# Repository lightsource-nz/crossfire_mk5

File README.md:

# crossfire

USB-MIDI forwarding between every instrument on the host port, with a small OLED status display.
Two tangible boards run it: a Pico 2 wearing the Pico-OLED-1.3, and the stock RP2040 Pico.

## Building

This project is built against the **light framework** checkout beside it (`../light_mk5`); set
`LIGHT_PATH` for another layout. The framework supplies the C shell, the portable crates, the
ports, the asset compilers and the shared script layer. Everything that is crossfire's own --
the application, the board modules, the version, the signing key, the flash map -- is here.

```
scripts/build.ps1 [-Target crossfire_pico2|crossfire_pico]
scripts/flash.ps1 -Target crossfire_pico2     # over SWD, through a debug probe
scripts/debug.ps1 -Target crossfire_pico2
scripts/console.ps1 -Port <COM>               # the console rides the probe's UART
scripts/test.ps1                              # the application's host tests
```

CI (`.github/workflows/ci.yml`) runs the same scripts through the framework's reusable workflows:
the host tests, and a firmware build of each board -- the Pico 2 leg with its bootloader -- whose
images are kept as artifacts.

## Images are signed

Every build signs its image and the device's flash map with `keys/dev.pem`, which is public and
protects nothing (see `keys/README.md`); a release is signed with a key that never appears here.
The flash map gives the application an A/B pair, so an update is written to the slot that is not
running and chosen on the next boot, and a data partition for the assets. What the hardware
verifies, and when, is specified in the framework's `documents/11-secure-boot-and-update.md`.

## A new image keeps itself only if it works

An update is started on probation: the Pico 2's boot ROM runs it once, and unless it commits itself
the previous image boots again -- at the next reset, or when the ROM's probation watchdog runs out
some seventeen seconds after the boot. crossfire makes that decision on its own
(`crates/light_app_crossfire/src/probation.rs`). At boot the board asks the ROM whether the running
image is a candidate; if so, the application watches itself for three seconds after every module has
loaded and commits once the main loop is turning over, the console core is alive, and the display
has taken a whole frame with no bus timeout. A panic, a stopped loop or a failed check means no
commit, and so the old firmware comes back; a candidate that has not passed by ten seconds of uptime
is given up on well inside the ROM's window. The console reports every step as `probation: ...`.
The RP2040 has no second slot and puts nothing on probation, so there every image is already kept.

## The production board

`pcb/` holds the hardware for the board this firmware is heading for -- an RP2350 hosting four
instruments through a hub, powered over USB-C, optionally with a radio and a battery. It is a KiCad
project with the blocks and their interfaces settled and no components placed yet, alongside the
power budget, the part selection and the two decisions the rest of the design hangs off. See
`pcb/README.md`. Nothing has been built or measured.

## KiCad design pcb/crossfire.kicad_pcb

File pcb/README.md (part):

# crossfire hardware

The production board: an RP2350 hosting four USB instruments through a hub, with one USB-C
connector that carries both its power and its link to a computer.

**Status: prototype, nothing built.** Every number below is a budget or a datasheet figure, not a
measurement. A predecessor design exists elsewhere as a sketch of an earlier vision; it was never
manufactured or validated, so nothing here is inherited from it — individual parts are reused only
where they stand up on their own.

**This is the reduced first design.** An earlier revision of this board carried a Power Delivery
sink on a second connector, a charger and a cell, and a radio. Those are deferred, not rejected: they
made a first board that was hard to lay out and harder to bring up, and none of them is needed to
prove the thing the product is for. That revision is kept whole in the history at commit `bb66643`.

## What the board has to do

- Host four USB-MIDI instruments at once, on four type-A receptacles, each supplied from the
  board's 5 V input.
- Keep the firmware that already exists: the USB device role and its console, and the signed A/B
  image pair with probation.
- Present itself to a computer on the upstream connector *while* hosting the instruments, so the two
  roles live on separate interfaces.
- Take all of its power from that same upstream USB-C connector, and share out whatever the source
  there offers between the four ports and its own electronics.

## Three decisions shape everything else

### 1. Two USB roles on two interfaces

The RP2350 has **one** USB controller, and the board needs two roles at once: host for the four
instruments, device for the computer on the upstream connector. The roles are kept apart on separate
interfaces — the hardware controller takes one, and a full-speed port built in PIO takes the other.
Nothing is multiplexed and nothing switches role, so a computer and the instruments are live at the
same time.

**The hardware controller faces outward as the device, and PIO hosts the hub.** The deciding
argument is recovery, and it beats the alternative on its own terms:

- **The boot ROM drives the hardware controller.** Putting that pair on the upstream connector means
  BOOTSEL and USB DFU work on the connector the product actually has. Recovery needs no debug probe,
  no case opened, nobody on the bench.
- **It makes the risky new thing the recoverable one.** The host side is what has to be rebuilt, and
  if that goes wrong the board can still be reflashed over its own port. The other way round, a rough
  device port takes the console and DFU with it and leaves only SWD.
- **Bring-up starts working rather than blocked.** The board is programmable and has a console over
  its own connector before any of the new firmware exists, so the host side can be brought up
  incrementally against a board that already talks.

What it costs, plainly: **the host role moves onto a new transport.** The existing host stack sits
behind a host-controller seam, so the stack, the hub handling and the MIDI layer above it are kept —
but the packet-level transport underneath becomes a full-speed USB host built in PIO, which does not
exist in this tree. That is the single largest piece of new firmware this board asks for, and it is
the harder of the two roles to build: it has to generate frames, schedule transactions across four
devices and a hub, and handle retries.

The device side, by contrast, is already proven on hardware — the console rides it today. The one
addition there is the computer-facing MIDI interface, which is a device class on a working stack.

**The upstream connector is unambiguous.** It sinks power and acts as a device, both, always — so
the CC lines mean one thing, there is no role to choose, and the charger-versus-computer guess that a
multiplexed design would have needed is gone. Electrically it is also the simpler end: the hardware
controller's pins carry their own impedance matching and pull-ups, so the pair needs only an ESD
array and the receptacle's two data pairs tied together, so a cable can go in either way up.

**The PIO port sets the system clock, and it sets it upward: 240 MHz.** Full-speed bit timing off PIO
wants a system clock that is an integer multiple of 12 MHz, so the state-machine divider is exact and
the bit period carries no fractional jitter. The stock 150 MHz is not such a multiple. Going *down* to
120 MHz would satisfy it at the cost of a fifth of the loop; going up to 240 MHz satisfies it and buys
the loop instead, and four things line up on that number:

- **12 MHz × 20.** Twenty system cycles per bit, and an exact divide by two if the state machine wants
  to run at 120 MHz. Either way the divider is an integer.
- **Twenty cycles a bit is a generous instruction budget** for the hardest software on the board. Ten
  would have been tight. The clock that makes the timing legal also makes the program easier to write.
- **It is already proven on this silicon.** A board in this codebase runs RP2350 at 240 MHz today,
  from the crystal through a 1440 MHz VCO and a divide by six, at stock core voltage.
- **The flash stays at its fastest legal clock.** A 133 MHz part divided by two off 240 MHz is
  120 MHz. Higher multiples are worse here, not better: 288 MHz would need a divide by three and drop
  the flash to 96 MHz.

So the constraint that looked like a tax is a 1.6× clock increase, and the forwarding loop gets
faster rather than slower. The device port is unaffected either way — its 48 MHz comes from the other
PLL.

**It is an overclock, though, and that is the part to weigh.** 240 MHz is above the datasheet's
150 MHz. It is proven on the boards in hand; it is not characterised across a production population
or a temperature range, and a product ships into both. What to establish before committing: whether
stock core voltage still holds at temperature, and what the fallback is if it does not — 192 MHz
(12 × 16) is the next multiple down that still beats stock, and 120 MHz is the floor that always
works.

The PIO port is the host end, so it carries 27 Ω series resistors on the pair and host-side
pull-downs; the 1.5 kΩ pull-up belongs to the hub, which asserts it on its own upstream port. It runs
entirely on the board, from GPIOs to the hub, and never reaches a connector or a cable — which is the
kindest possible first home for a software-timed USB port.

One consequence of hosting on-board: **no host supplies VBUS to the hub's upstream port**, so the hub
is self-powered, and its upstream-detect input is driven by the MCU. The datasheet is explicit about
this case: a *detachable* hub divides that pin down from the upstream VBUS, but a self-powered hub
with a permanently attached host takes it "from a dedicated host control output, or the 3.3 V domain
that powers the host" — so a GPIO, which costs one pin and hands the firmware the ability to hold
the hub down until it is ready and to force a re-enumeration by toggling it. Without that pin
asserted the hub never believes it is connected.

### 2. One upstream connector, and its 5 V is the board's 5 V

Power and data arrive on **one USB-C receptacle**. Its data pair goes to the processor's hardware
controller, as above. Its VBUS *is* the 5 V rail: it feeds the four port switches directly and a
small buck converter that makes 3.3 V for everything else. There is no power path to manage, no
second source to keep apart from the first, and nothing between the connector and a port except that
port's own switch.

| | receptacle | carries |
| --- | --- | --- |
| upstream | type-C, USB 2.0, 16-pin | D+/D− to the hardware controller, Rd on both CC pins, ESD, VBUS as the 5 V rail |

**What that gives up is stated here rather than discovered later.**

- **The ports get what the cable delivers, not a regulated 5 V.** A source is allowed to be as low
  as 4.75 V at its own connector and a cable may drop half a volt more at 3 A, so a port can see
  about 4.2 V in the worst case with every port loaded through a poor cable. Class-compliant MIDI
  instruments draw a fraction of that current, where the drop is tens of millivolts, so this is a
  limit to state rather than one expected to bite.
- **The power available is 15 W at most**, because nothing on the board can ask for more than 5 V.
  That is exactly enough for four ports at full USB 2.0 current and the electronics, with about
  three quarters of an amp to spare.
- **A computer is now the power source as well as the host**, and most computers offer far less than
  3 A. That is what the third decision is about.
- **Nothing protects the rail from a source that misbehaves.** A compliant source stays at 5 V
  because this board never negotiates for anything else, and the port switches are 6 V parts. A
  charger that puts 9 V or more on VBUS unasked would damage them. That was a risk the earlier
  design's input switches removed; here it is accepted.

**The capacitance the source sees at plug-in is kept to what USB allows.** A device may present no
more than 10 µF to VBUS when it is attached. Everything permanently on the rail counts: the buck's
input capacitor, the bypass at each port switch, the one at the connector. That comes to 10.6 µF as
printed on the parts and noticeably less in circuit, since a 10 µF ceramic keeps perhaps two thirds
of itself at 5 V. Each port's 22 µF sits *behind* its switch, so it is charged through a current
limit when the hub turns that port on, not by the plug going in.

### 3. The source says what it can supply, and the firmware divides it

Four ports at full USB 2.0 current is 2 A, and the board itself takes about a quarter of an amp. A
USB-C source states how much it will supply through the CC line, and the three answers it can give
are very different budgets:

| the source advertises | the board takes | left for the four ports |
| --- | --- | --- |
| 3 A | 0.25 A | 2.75 A — every port at its full 500 mA |
| 1.5 A | 0.25 A | 1.25 A — four typical instruments, or two at full current |
| USB default (0.5 A, or 0.9 A on a USB 3 port) | 0.25 A | 0.25–0.65 A — one or two instruments |

**So the processor reads the CC lines, and port power is policy.** Each CC pin already carries the
5.1 kΩ that marks this board as a sink. The voltage the source's pull-up produces across that
resistor is the advertisement: under 0.61 V is the default, 0.70–1.16 V is 1.5 A, and 1.31–2.04 V
is 3 A. Both pins go to ADC inputs, each through 10 kΩ with 100 nF to ground at the pin, and the
firmware takes the higher of the two — the cable connects only one.

The firmware then decides which ports to power. The hub already switches each port's power on
request and reports over-current port by port, so enforcing a budget is a matter of which ports the
host stack turns on, using requests it already makes. The 1 A threshold in each port switch protects
the hardware; the policy decides what is offered.

**The sense must not load the line it reads.** A divider across CC would sit in parallel with the
5.1 kΩ and change what the source believes it is talking to, which is worse than not knowing the
answer. A series resistor into a capacitor draws nothing at DC, so the termination stays exactly
5.1 kΩ. That holds only while the processor's pad draws nothing either, which makes one firmware
requirement: **the digital input on those two pads stays disabled.** They are read by the ADC only.

## Block structure

```mermaid
graph LR
  C[USB-C upstream] <-->|data, hardware device| MCU
  C -->|VBUS, 5 V| R5[5 V rail]
  C -.->|CC1, CC2| MCU
  R5 -->|5 V| P[4 port switches and type-A]
  R5 --> B33[buck 3.3 V]
  B33 --> MCU[RP2350A and flash]
  B33 --> HUB[4-port hub]
  MCU <-->|data, PIO host| HUB
  HUB <-->|data| P
  HUB -.->|port power, overcurrent| P
```

*Solid lines carry power or USB data; dashed lines are control and sensing.*

## Power

### Rails

| rail | source | sized for | why |
| --- | --- | --- | --- |
| 5 V | the upstream connector's VBUS, directly | 3 A | the ports and the buck; whatever the source and the cable deliver |
| 3.3 V | fixed-output buck from 5 V | 2 A part, 0.35 A needed | a buck rather than a linear regulator saves about 80 mA of an input budget that can be as small as half an amp |
| 1.1 V (core) | the MCU's own switching regulator | — | not a board converter, but it needs board parts: an inductor on `VREG_LX` and a feedback network, which is why it is a rail and not just decoupling |

The core rail catches people out, so it is worth stating: this MCU regulates its own core with a
*switching* regulator, not a linear one. It brings out `VREG_VIN`, `VREG_LX` and `VREG_FB`, so the
schematic carries an inductor and the rail it makes feeds the `DVDD` pins. The analogue supply for
the ADC wants its own filter off 3.3 V as well, and it now has work to do: the two CC readings come
through it.

**The 3.3 V converter is a fixed-output part, so it has no divider to get wrong.** It takes an input
capacitor, a bootstrap capacitor, an inductor and its output capacitors, and its enable is tied to
its input so it starts when the cable goes in. Its input range reaches well above anything VBUS
should carry and down to 3.8 V, which is below the lowest the cable can leave it with.

### Budget

**3.3 V rail**

| | typical | peak |
| --- | --- | --- |
| RP2350A, both cores at 240 MHz, USB active | 110 mA | 150 mA |
| QSPI flash, executing in place | 15 mA | 25 mA |
| hub | 90 mA | 120 mA |
| indicators, crystals, pull-ups | 25 mA | 40 mA |
| **total** | **240 mA** (0.79 W) | **335 mA** (1.1 W) |

At about 90% conversion that is **175 mA typical and 250 mA peak from the 5 V input**.

**5 V rail**

| | current | power |
| --- | --- | --- |
| full USB 2.0 spec, 4 × 500 mA | 2.00 A | 10.0 W |
| four typical MIDI instruments | 0.4–1.0 A | 2–5 W |
| the 3.3 V converter's input | 0.18–0.25 A | 0.9–1.25 W |

**Upstream**

Worst case is 2.25 A at 5 V, which a 3 A source covers with margin. A 1.5 A source runs four
ordinary instruments. A default port runs the board and one or two instruments, and it is the
firmware's reading of CC that tells those three cases apart.

## Parts

Stock KiCad symbols exist for everything marked with one; the rest need drawing.

| block | part | symbol | why |
| --- | --- | --- | --- |
| MCU | RP2350A, QFN-60 | `MCU_RaspberryPi:RP2350A` | 30 GPIO is enough (see below); RP2350B if a display is added |
| flash | W25Q128JVS, 16 MB | `Memory_Flash:W25Q128JVS` | the A/B image pair plus the asset partition; 2 MB would not hold it, and its 133 MHz rating covers the 120 MHz the divider lands on |
| hub | USB2514B | `Interface_USB:USB2514B_Bi` | four downstream ports, per-port power and overcurrent pins, no external EEPROM needed |
| port switch ×4 | TPS2065C | `Power_Management:TPS2065CDBV` | 1 A threshold, **active-high enable, open-drain fault** — what the hub needs at both ends. It limits by going into constant current rather than latching off, and adds reverse blocking and output discharge, both of which a port wants. Its 0.5 A sibling is the same trap as before: that is the budget itself, with nothing for inrush |
| port data ESD ×4 | 2-channel array, low capacitance | — | needed because the switch above protects power only. The TPD3S0x4 would have covered both, but it has no fault output, so it cannot tell the hub anything |
| 3.3 V | AP63203WU | `Regulator_Switching:AP63203WU` | fixed 3.3 V, 2 A, input to 32 V and down to 3.8 V; no feedback divider, six pins |
| upstream data ESD | 2-channel array, low capacitance | — | the downstream pairs get theirs from the port switch; the upstream pair has no such part in front of it |
| upstream connector | USB-C 2.0, 16-pin | `Connector:USB_C_Receptacle_USB2.0_16P` | power and data both |
| CC sense ×2 | 10 kΩ and 100 nF | `Device:R_Small`, `Device:C_Small` | one pair per CC pin, into an ADC input; in series, so the 5.1 kΩ termination is not loaded |
| port connectors ×4 | type-A | `Connector:USB_A` | |

Two notes on the hub. Its upstream link runs at full speed, because the RP2350's controller is
full-speed only — so the whole tree is full speed and instruments that could do high speed fall
back, which costs nothing, as USB-MIDI 1.0 is a full-speed class. And the hub drives the port
switches itself: `PRTPWR[1:4]` to each switch's enable, each switch's fault back to `OCS_N[1:4]`. Port
power then goes on and off through ordinary hub requests that any host stack already makes,
overcurrent arrives as a standard port status change, and eight GPIOs stay free.

### Passives

A value on its own is not a specification, so every capacitor carries a **voltage rating and a
dielectric**, chosen from the net it sits on rather than from a house default. The rule is at least
twice the working voltage, rounded to a standard rating, and never below what a socket the user can
reach is able to present.

| what it decouples | rating | dielectric |
| --- | --- | --- |
| 3.3 V, the bootstrap and the internal filter nodes | 16 V | X7R |
| the core rail and the regulator's own capacitors (1.1 V and 3.3 V, 4.7 uF in 0402) | **6.3 V** | X5R |
| the 5 V rail and each port's own output | 25 V | X7R |
| the connector side — the capacitor at the receptacle and the two on the CC senses | **50 V** | X7R |
| crystal loads | 50 V | **C0G** |

**The 5 V rail is now a connector-side rail**, since nothing stands between it and the receptacle.
Its capacitors are rated 25 V for that reason and not because 5 V asks for it.

**Resistors carry a tolerance, and it is 1% only where the value is read**: a reference a part
trims itself against, a divider ratio, a termination that states what this end of a cable is. The
rest are pull-ups, pull-downs, straps and series parts, where 5% is honest and 1% is a cost with
nothing on the other side of it. Power is not a field: the largest dissipation anywhere on the
board is a few milliwatts in an indicator's series resistor, so the smallest standard part covers
every one of them.

**The two inductors are specified by what they have to carry, not by their value alone.**

| | value | has to stay unsaturated to | why that number |
| --- | --- | --- | --- |
| core regulator | 3.3 uH +/-20% | **1.5 A** | the processor's own datasheet says so, along with a 250 mohm ceiling on resistance |
| 3.3 V buck | 4.7 uH | **2 A** | the load is a third of an amp, but the converter limits at well over 2 A and the inductor should not be what gives way first |

**The core regulator's inductor has a requirement that is easy to lose**: it must be fully shielded
and **marked for polarity**, and oriented the way the vendor's layout shows. Their own note is that
stray field from the inductor couples into the regulator's control loop and moves the output even
with nominally shielded parts. That is a placement constraint arriving from a component datasheet,
so it is recorded here where layout will look for it.

**The crystals are specified by load, not just frequency**, because the load is what decides
whether they oscillate on frequency at all. Both work out at **10 pF**, and both vendors name the
arithmetic rather than leaving it to be guessed.

The processor's is simply stated: its vendor recommends a specific part and publishes its
parameters, 10 pF load and +/-30 ppm either side. The hub's has to be derived, and the derivation
is the part worth writing down, because the obvious way to do it is wrong. Stray capacitance sits
in parallel with **each** loading capacitor, not with the two of them in series -- so the load is
not half the pair plus the stray, it is half of *(the pair plus the stray)*. With the 18 pF the
hub's own documents call typical and a few picofarads of board stray, that is about **10.5 pF**,
and the nearest standard part is 10 pF. The naive arithmetic gives 12 pF, which is a different
part. Both of the vendor's two formulations -- the older datasheet's and the newer checklist's --
agree on this once they are read carefully.

Its frequency allowance is **+/-350 ppm**, and that number is a trap in the other direction: it is
the *total* the hub can tolerate, so a part sold as +/-350 ppm would spend the entire budget before
temperature and ageing are counted. A commodity +/-50 ppm part meets it several times over.

**There is no feedback resistor across either crystal, and none is wanted.** The hub's datasheet
figure draws a 1 Mohm across the pins without saying which side of the package it is on; its
design checklist, which exists to list what the board has to provide, asks only for the two
loading capacitors. The same checklist confirms two things already drawn: the 12.0 kohm 1%
reference to ground, and that the reset line may be held by the processor rather than pulled up,
which is what the pull-down and the GPIO on it amount to.

### Mechanical, and the connectors

**The enclosure is drawn around the board, not the board around an enclosure**, and the first one
runs bare on a bench. That ordering decides more than it sounds like: the board may take whatever
outline suits it, but it has to be usable with nothing around it, so parts that are pressed or
looked at face upwards rather than sideways, and anything that takes a plug's insertion force goes
through the board rather than resting on pads.

**One constraint fixes the board's width, and it is the port pitch.** Four type-A receptacles at
**25.4 mm between centres** span 76.2 mm centre to centre. The widest stock footprint for a
full-size horizontal receptacle occupies 22.8 mm and the narrowest 15.4 mm, so every one of them
fits the pitch -- the narrow end leaving about 10 mm of clear board between neighbours, which is
where each port's switch, its protection array and its bulk capacitor have to live. Taking the
narrow one, the four ports occupy 91.6 mm of courtyard, and with a few millimetres of edge each
side **the port edge cannot be shorter than about 100 mm**. That is now a fixed dimension of the
product, not an outcome of layout.

It is worth recording *why* 25.4 mm rather than something tighter, because it looks generous
against a 13 mm receptacle and invites being trimmed later. The number is not about the
receptacle, it is about the **plug**: a moulded type-A plug is commonly 16 to 20 mm across, so a
narrower pitch yields a hub whose four ports cannot all be used at once. That is the failure this
product exists to avoid.

| | part | why |
| --- | --- | --- |
| downstream ports x4 | full-size type-A, horizontal, **through-hole** | the plug's force goes into the board. Every stock option is through-hole, which settles it |
| upstream | 16-pin type-C, surface pads with **through-hole shell tabs** | the signal pads are fine surface mount; the shell takes the strain through the board |
| indicators | 0603, **red and green** | the 1 kohm series resistor rules out the high-voltage colours |
| buttons x3 | 6 mm surface-mount tactile, top-actuated | one part for all three, pressable on a bare board |
| debug | 5-pin header on 2.54 mm | bench-first means a header that any probe's flying leads reach |

**The indicators' series resistor has already chosen their colour, which is worth noticing before
someone fits a blue one.** They run from a 3.3 V pin through 1 kohm, so the current depends entirely
on the forward voltage: about **1.3 mA** for red, amber or ordinary green, and about **0.3 mA** for
true green, blue or white, which is not enough to rely on seeing. The low-voltage colours are
therefore not a preference here, they are a requirement of the resistor already drawn. Taken as
**red and green**; swapping to blue or white means changing the resistor too, and at that supply
there is very little headroom left to do it with.

1.3 mA is deliberately modest rather than accidental -- a modern part is clearly visible at it
indoors, and on a source that may offer half an amp it is not worth spending more.

**The three buttons are one part, surface mount, top-actuated, at the edge.** One line item covers
all three, a 6 mm actuator is comfortable to press on a bare board, and an enclosure then wants a
hole rather than a plunger. Two notes for whoever draws that enclosure: the user button is the only
one an owner should be able to reach, since the other two put the board into its bootloader and
reset it, so recessing them is reasonable even though all three sit on the same edge. And the user
button has **no pull-up on the board** -- it relies on the processor's internal one being enabled,
which is ordinary, but it means the pin reads as floating until firmware has configured it.

**Four M3 mounting holes, plated and bonded to ground.** Bonded rather than bare because the
asymmetry favours it: five connector shells on this board are already at ground, so if the enclosure
is metal a screw into a metal standoff should join that system deliberately rather than through
whatever it happens to touch, and if the enclosure is plastic the bond does nothing and costs
nothing. The decision that cannot be undone without a new board is the one to leave the pads off.

**Two go in the back corners and two go between the sockets.** Each needs about 7 mm of clear
diameter, because an M3 head is 5.5 mm and a washer 7 mm, and a hole only the drill clears is one
that cannot be done up. The gap between one socket's body and the next is 8.1 mm, which takes a hole
with half a millimetre to spare each side -- so the front pair sit in the first and third gaps,
under 4 mm from the front edge, right where a plug is pushed in. That is better than the earlier
arrangement could manage, where nothing came within 16 mm of the socket row and the enclosure had to
carry it on a ledge.

| | position | |
| --- | --- | --- |
| H1 | 4.0, 4.0 | back left corner |
| H2 | 96.2, 3.8 | back right corner, beside the buttons |
| H3 | 24.6, 49.5 | between the first and second sockets |
| H4 | 75.4, 49.5 | between the third and fourth |

**Each capacitor's package is chosen from how much of it has to survive its own bias.** The
question is not how much capacitance is printed on the part but how much is there once the voltage
is across it. On this board the question has an upper bound as well as a lower one: the 10 uF at the
buck's input is in 0603, which keeps enough of itself at 5 V for the converter and loses enough to
stay inside what USB allows a device to present at attach. The 22 uF parts at the 3.3 V output are
in 0603 too, on a 3.3 V rail they are a long way up their own curves; the ones at each port are
1206. Decoupling goes to 0402, where being close to the pin matters more than the package.

**The processor's regulator takes the vendor's parts, not ours.** Its own hardware design guide
puts 4.7 uF in **0402** on the regulator's input (`VREG_VIN`), on its output (the core rail), and
on its analogue supply -- and the analogue supply is fed through **33 ohms** from 3.3 V, because
"the VREG_AVDD supply is very sensitive to noise, and therefore needs to be filtered" and draws
only about 200 uA. This board had the input and output capacitors as 10 uF and 4.7 uF in 0805, and
no filter at all. All three are now as the vendor has them (C4, C17, and R9 with C15), which also
takes two parts from 3.5 x 2 mm down to 1.9 x 1 mm beside the pin field, which is where there was
no room. The filter is 100 ohms and 1 uF rather than the vendor's 33 ohms and 4.7 uF: the same
corner frequency, 20 mV of drop at 200 uA, and a capacitor that exists in 0402 at 6.3 V -- and it
sits outside the regulator's loop, because at 200 uA the few millimetres of track from the pin to
the filter cost nothing. The same guide accepts one 100 nF shared between `USB_OTP_VDD` and `QSPI_IOVDD` for the
same reason, and places the boot button's resistor at the flash.

### Footprints

**Every part carries a footprint.** Most are decided the moment the part is -- a SOT-23-5 is a
SOT-23-5 -- and the capacitors' came out of the reasoning above. The resistors are all 0402. They
were 0603, on the argument that the first board runs bare on a bench and a part you can get a probe
or an iron onto is worth the millimetre; beside two fine-pitch parts the millimetre turned out to be
worth more. Nothing electrical changes: the largest dissipation in any of them is a few milliwatts
against a sixteenth of a watt. The two indicators stay 0603, since they are there to be seen.

**A footprint chosen by body size and pin count is not checked.** The hub's was wrong by 0.2 mm in
each direction when it was picked that way. Its datasheet tabulates a **recommended** land pattern,
not merely a package outline, and names a 3.70 mm pad where the provisional entry had 3.90. Too
large is the direction that floats a part off its pins on reflow. Neither error of that kind shows
in the schematic, the connection list or any rules check -- only on a board that does not assemble
properly -- and the drawings that settle it are graphics with no text to extract, so they have to be
rendered and read rather than searched.

**Two footprints come from the processor vendor's own reference design**, which is published under
a permissive licence and carried into this project's footprint library with the notice that licence
asks for. One is the core inductor's. The other is the **processor's own land pattern**: the pad
under that part is the pattern its maker lays out, not a guess at the nearest library variant.

| | part | why |
| --- | --- | --- |
| core regulator inductor | Abracon AOTA-B201610S3R3-101-T | the processor's vendor names it, and publishes a layout built around it |
| 3.3 V buck inductor | a 4.7 uH part in the 4 mm shielded family already on the board | the land pattern was already in the project; the exact part number is still to be confirmed against its saturation figure |

**The board carries its name on the front silkscreen**: the application's graphic, 21 x 15.5 mm
in the open area right of the hub, with `CROSSFIRE Rev ${REVISION}` beneath it, the revision read
from the board's title block so a new revision is one field change. The graphic is a footprint in
the project library, `crossfire_logo`, traced from `art/crossfire-logo.png` by
`scripts/png2silk.py`: ink thickened at full resolution so the thinnest stroke prints at 0.2 mm,
then scaled to 0.1 mm pixels and written as filled rectangles. Regenerate it from the script, not
by hand, if the artwork changes.

**The socket's and the receptacle's footprints are project copies of the library's**, differing
only in their silkscreen.
The library draws the whole body, including the 3.7 mm that stands beyond the board edge, and the
rules check reports every silk line that crosses the edge. The copy stops its silkscreen 0.4 mm
inside the edge marking; pads, courtyard and fabrication drawing are the library's.

### GPIO budget

Twelve of the thirty, and the assignment is not arbitrary — the PIO pair is forced adjacent and the
rest fall out of keeping peripherals on their default pins.

| GPIO | net | why there |
| --- | --- | --- |
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
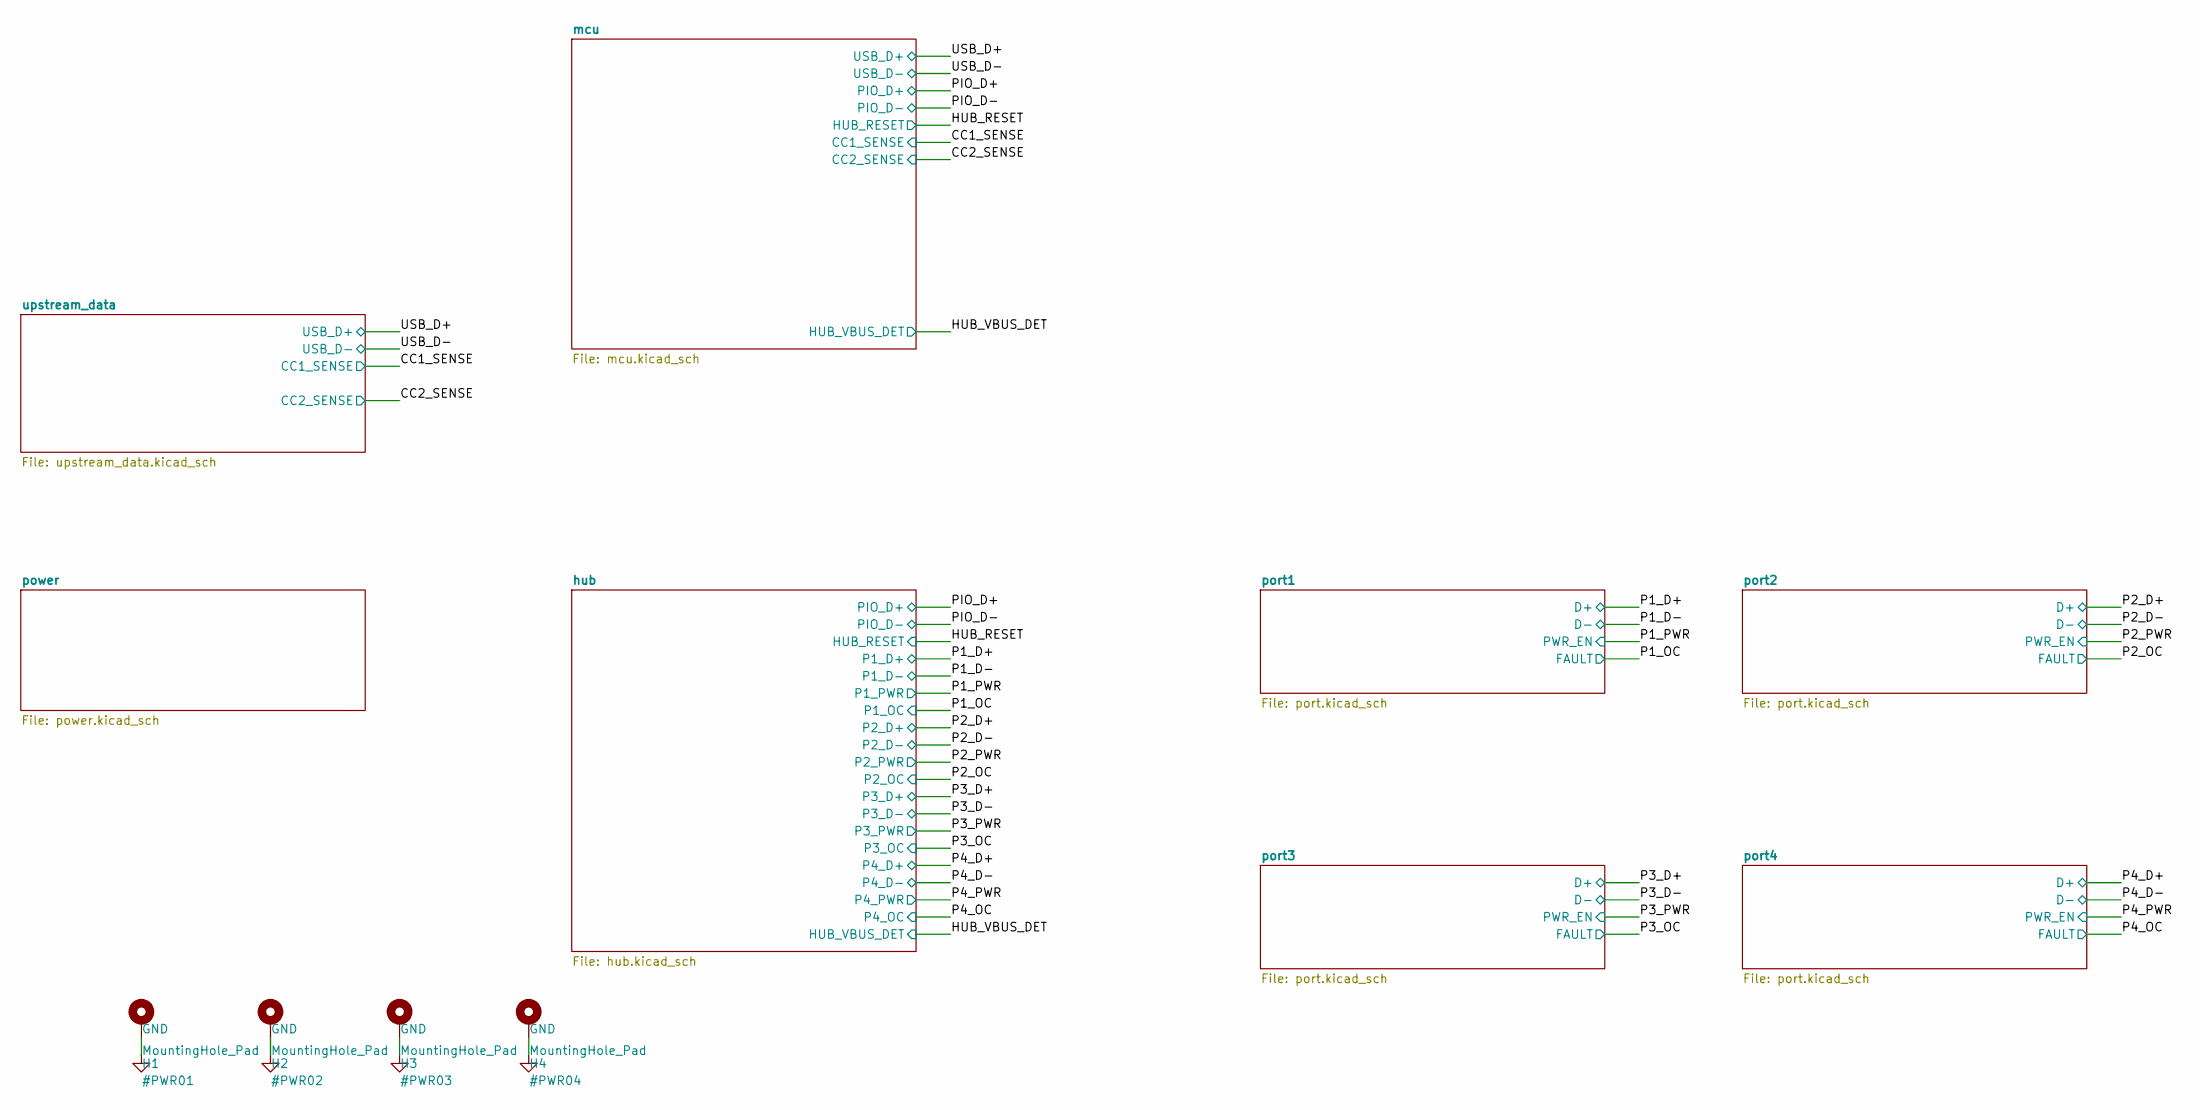
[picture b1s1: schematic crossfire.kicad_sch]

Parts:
H1, H2, H3, H4: MountingHole_Pad; MountingHole_3.2mm_M3_Pad

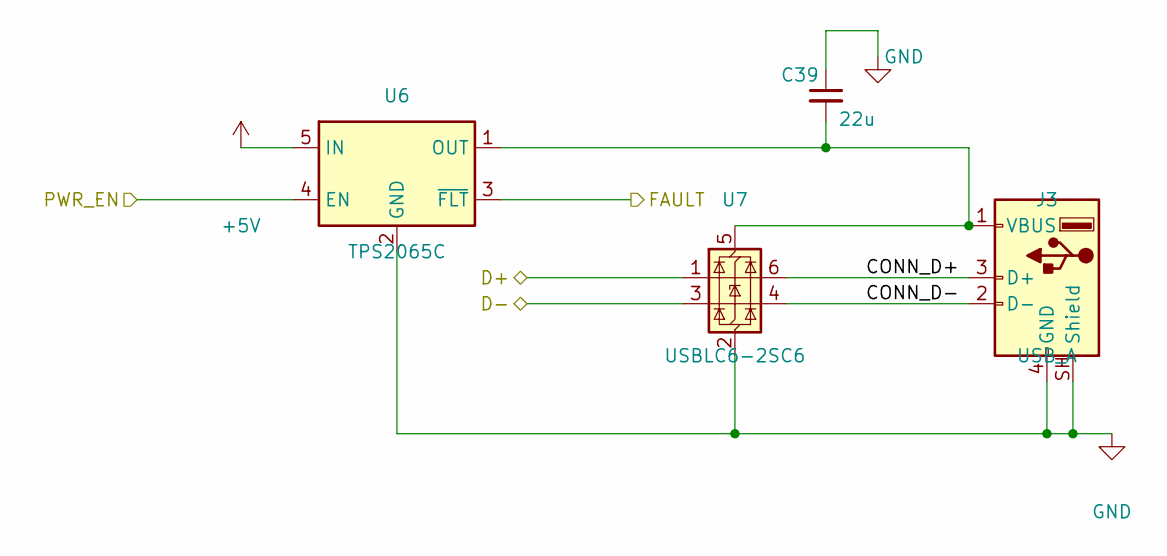
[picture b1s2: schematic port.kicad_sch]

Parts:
C39: 22u; C_1210_3225Metric; Voltage 25V
J3: USB_A; USB_A_Molex_67643_Horizontal_Overhang; MPN TE 292303-6; LCSC C591765
U6: TPS2065C; SOT-23-5; MPN TPS2065CDBVR; LCSC C353882
U7: USBLC6-2SC6; SOT-23-6; MPN USBLC6-2SC6; LCSC C7519

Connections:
+5V: U6.5 (IN); also elsewhere on the board
/P1_D+: U7.1 (I/O1); also elsewhere on the board
/P1_D-: U7.3 (I/O2); also elsewhere on the board
/P1_OC: U6.3 (~FLT); also elsewhere on the board
/P1_PWR: U6.4 (EN); also elsewhere on the board
/port1/CONN_D+: J3.3 (D+), U7.6 (I/O1)
/port1/CONN_D-: J3.2 (D-), U7.4 (I/O2)
unnamed: C39.2, J3.1 (VBUS), U6.1 (OUT), U7.5 (VBUS)

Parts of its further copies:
C40, C41, C42: 22u; C_1210_3225Metric; Voltage 25V
J4, J5, J6: USB_A; USB_A_Molex_67643_Horizontal_Overhang; MPN TE 292303-6; LCSC C591765
U8, U10, U12: TPS2065C; SOT-23-5; MPN TPS2065CDBVR; LCSC C353882
U9, U11, U13: USBLC6-2SC6; SOT-23-6; MPN USBLC6-2SC6; LCSC C7519

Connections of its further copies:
+5V: U8.5 (IN), U10.5 (IN), U12.5 (IN); also elsewhere on the board
/P2_D+: U9.1 (I/O1); also elsewhere on the board
/P2_D-: U9.3 (I/O2); also elsewhere on the board
/P2_OC: U8.3 (~FLT); also elsewhere on the board
/P2_PWR: U8.4 (EN); also elsewhere on the board
/P3_D+: U11.1 (I/O1); also elsewhere on the board
/P3_D-: U11.3 (I/O2); also elsewhere on the board
/P3_OC: U10.3 (~FLT); also elsewhere on the board
/P3_PWR: U10.4 (EN); also elsewhere on the board
/P4_D+: U13.1 (I/O1); also elsewhere on the board
/P4_D-: U13.3 (I/O2); also elsewhere on the board
/P4_OC: U12.3 (~FLT); also elsewhere on the board
/P4_PWR: U12.4 (EN); also elsewhere on the board
/port2/CONN_D+: J4.3 (D+), U9.6 (I/O1)
/port2/CONN_D-: J4.2 (D-), U9.4 (I/O2)
/port3/CONN_D+: J5.3 (D+), U11.6 (I/O1)
/port3/CONN_D-: J5.2 (D-), U11.4 (I/O2)
/port4/CONN_D+: J6.3 (D+), U13.6 (I/O1)
/port4/CONN_D-: J6.2 (D-), U13.4 (I/O2)
unnamed: C40.2, J4.1 (VBUS), U8.1 (OUT), U9.5 (VBUS)
unnamed: C41.2, J5.1 (VBUS), U10.1 (OUT), U11.5 (VBUS)
unnamed: C42.2, J6.1 (VBUS), U12.1 (OUT), U13.5 (VBUS)

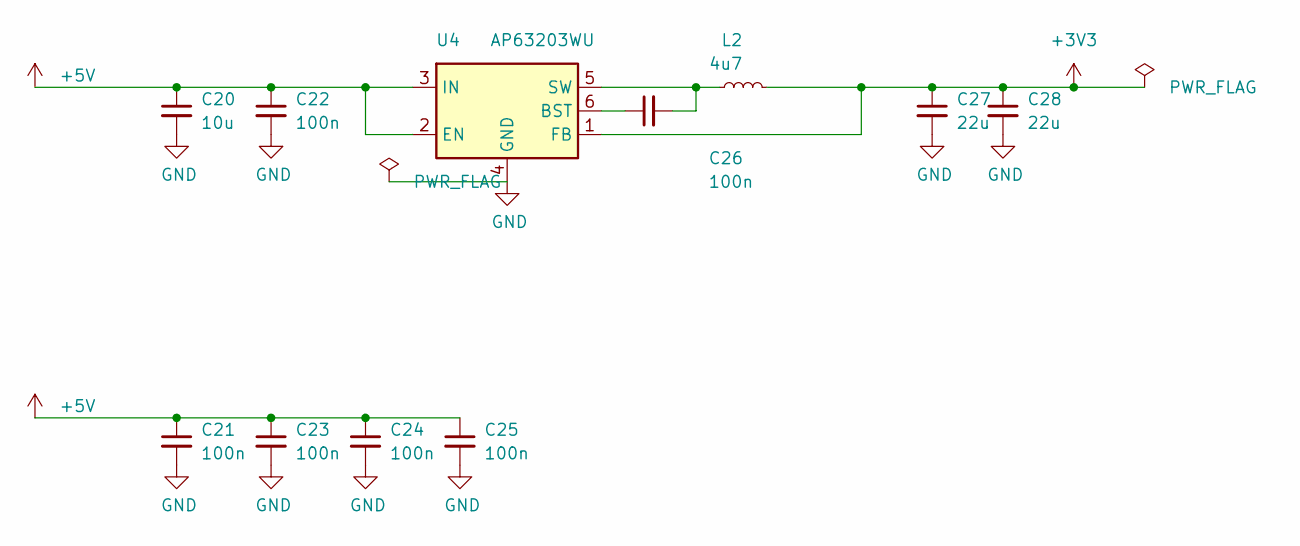
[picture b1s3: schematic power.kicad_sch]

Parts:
C20: 10u; C_0805_2012Metric; Voltage 16V
C21, C22, C23, C24, C25: 100n; C_0402_1005Metric; Voltage 25V
C26: 100n; C_0402_1005Metric; Voltage 16V
C27, C28: 22u; C_0603_1608Metric; Voltage 6.3V
L2: 4u7; L_Coilcraft_XxL4030; Tolerance 20%; MPN Sunlord SWPA4030S4R7MT; LCSC C57269
U4: AP63203WU; TSOT-23-6; MPN AP63203WU-7; LCSC C780769

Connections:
+5V: C20.1, C21.1, C22.1, C23.1, C24.1, C25.1, U4.2 (EN), U4.3 (IN); also elsewhere on the board
unnamed: C26.1, U4.6 (BST)
unnamed: C26.2, L2.1, U4.5 (SW)

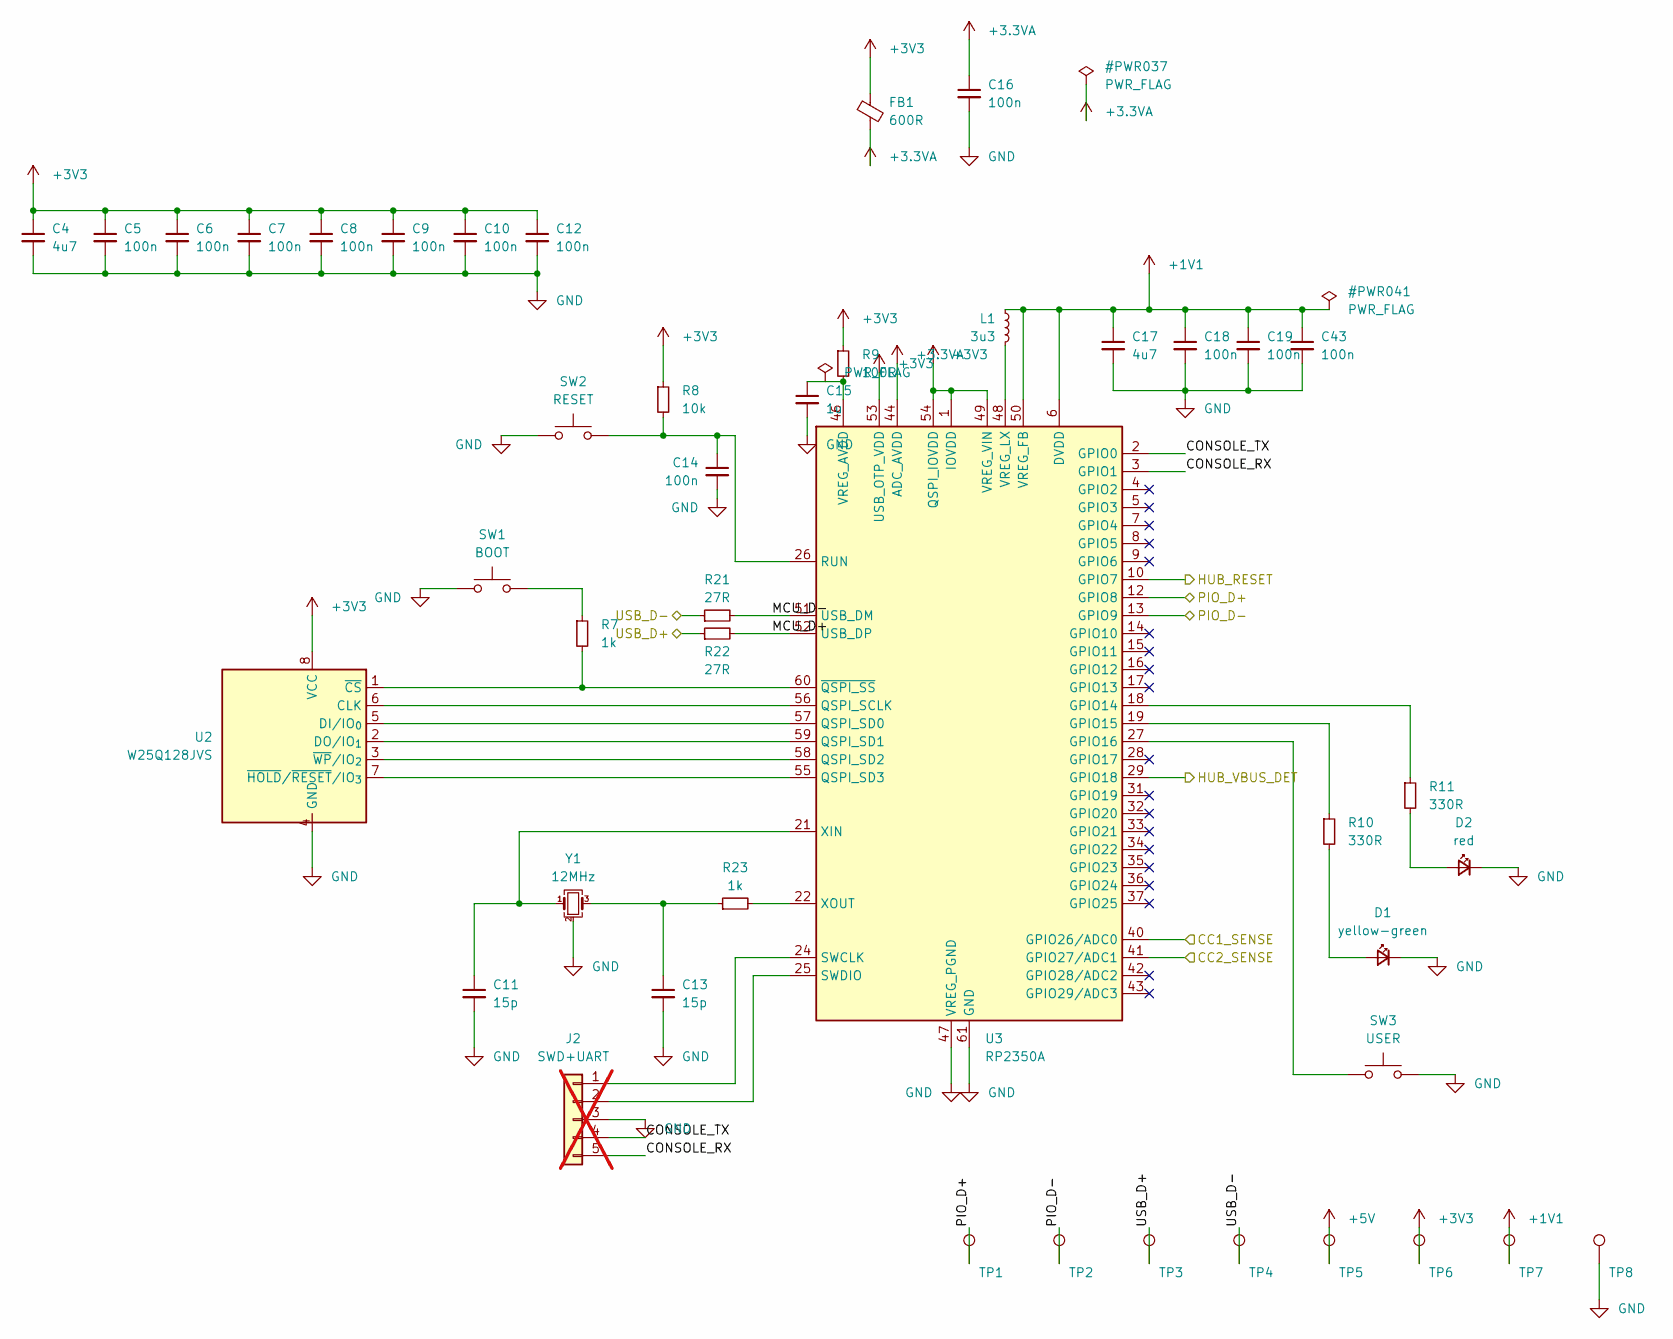
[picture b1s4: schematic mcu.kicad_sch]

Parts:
C4, C17: 4u7; C_0402_1005Metric; Voltage 10V; MPN Samsung CL05A475MP5NRNC; LCSC C23733
C5, C6, C7, C8, C9, C10, C12, C14, C16, C18, C19, C43: 100n; C_0402_1005Metric; Voltage 16V
C11, C13: 15p; C_0402_1005Metric; Voltage 50V
C15: 1u; C_0402_1005Metric; Voltage 16V; MPN Samsung CL05A105KO5NNNC; LCSC C29266
D1: yellow-green; LED_0603_1608Metric; MPN LITEON LTST-C194KGKT; LCSC C913102
D2: red; LED_0603_1608Metric; MPN KENTO KT-0603R; LCSC C2286
FB1: 600R; L_0603_1608Metric; Tolerance 25%; MPN Murata BLM18KG601SN1D; LCSC C85833
J2: SWD+UART; PinHeader_1x05_P2.54mm_Vertical; MPN 2.54 mm 1x5 header, not fitted; not fitted
L1: 3u3; abracon_aota-b201610s3r3-101-t; Tolerance 20%; MPN Abracon AOTA-B201610S3R3-101-T; LCSC C42411119
R7: 1k; R_0402_1005Metric; Tolerance 5%
R8: 10k; R_0402_1005Metric; Tolerance 5%
R9: 100R; R_0402_1005Metric; Tolerance 5%
R10, R11: 330R; R_0402_1005Metric; Tolerance 5%; MPN UNI-ROYAL 0402WGF3300TCE; LCSC C25104
R21, R22: 27R; R_0402_1005Metric; Tolerance 1%; MPN UNI-ROYAL 0402WGF270JTCE; LCSC C25100
R23: 1k; R_0402_1005Metric; Tolerance 1%
SW1: BOOT; SW_Push_1P1T_NO_CK_KSC6xxJ; MPN C&K KSC221JLFS; LCSC C221726
SW2: RESET; SW_Push_1P1T_NO_CK_KSC6xxJ; MPN C&K KSC221JLFS; LCSC C221726
SW3: USER; SW_Push_1P1T_NO_CK_KSC6xxJ; MPN C&K KSC221JLFS; LCSC C221726
TP1, TP2, TP3, TP4, TP5, TP6, TP7, TP8: TestPoint; TestPoint_Pad_1.0x1.0mm
U2: W25Q128JVS; SOIC-8_5.3x5.3mm_P1.27mm; MPN W25Q128JVSIQ; LCSC C97521
U3: RP2350A; rpi_rp2350a_vias; MPN RP2350A; LCSC C42411118
Y1: 12MHz; Crystal_SMD_3225-4Pin_3.2x2.5mm; Tolerance 30ppm; MPN JGHC S3212000101080; LCSC C390763

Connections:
+5V: TP5.1; also elsewhere on the board
/CC1_SENSE: U3.40 (GPIO26/ADC0); also elsewhere on the board
/CC2_SENSE: U3.41 (GPIO27/ADC1); also elsewhere on the board
/HUB_RESET: U3.10 (GPIO7); also elsewhere on the board
/HUB_VBUS_DET: U3.29 (GPIO18); also elsewhere on the board
/PIO_D+: TP1.1, U3.12 (GPIO8); also elsewhere on the board
/PIO_D-: TP2.1, U3.13 (GPIO9); also elsewhere on the board
/USB_D+: R22.1, TP3.1; also elsewhere on the board
/USB_D-: R21.1, TP4.1; also elsewhere on the board
/mcu/CONSOLE_RX: J2.5, U3.3 (GPIO1)
/mcu/CONSOLE_TX: J2.4, U3.2 (GPIO0)
/mcu/MCU_D+: R22.2, U3.52 (USB_DP)
/mcu/MCU_D-: R21.2, U3.51 (USB_DM)
unnamed: C13.1, R23.1, Y1.3
unnamed: D1.2 (A), R10.2
unnamed: D2.2 (A), R11.2
unnamed: J2.1, U3.24 (SWCLK)
unnamed: J2.2, U3.25 (SWDIO)
unnamed: R7.1, SW1.2
unnamed: U2.6 (CLK), U3.56 (QSPI_SCLK)
unnamed: U2.5 (DI/IO_{0}), U3.57 (QSPI_SD0)
unnamed: U2.2 (DO/IO_{1}), U3.59 (QSPI_SD1)
unnamed: R7.2, U2.1 (~CS), U3.60 (~QSPI_SS)
unnamed: U2.7 (~HOLD/~RESET/IO_{3}), U3.55 (QSPI_SD3)
unnamed: U2.3 (~WP/IO_{2}), U3.58 (QSPI_SD2)
unnamed: R11.1, U3.18 (GPIO14)
unnamed: R10.1, U3.19 (GPIO15)
unnamed: SW3.1, U3.27 (GPIO16)
unnamed: C14.1, R8.2, SW2.2, U3.26 (RUN)
unnamed: L1.2, U3.48 (VREG_LX)
unnamed: C11.1, U3.21 (XIN), Y1.1
unnamed: R23.2, U3.22 (XOUT)

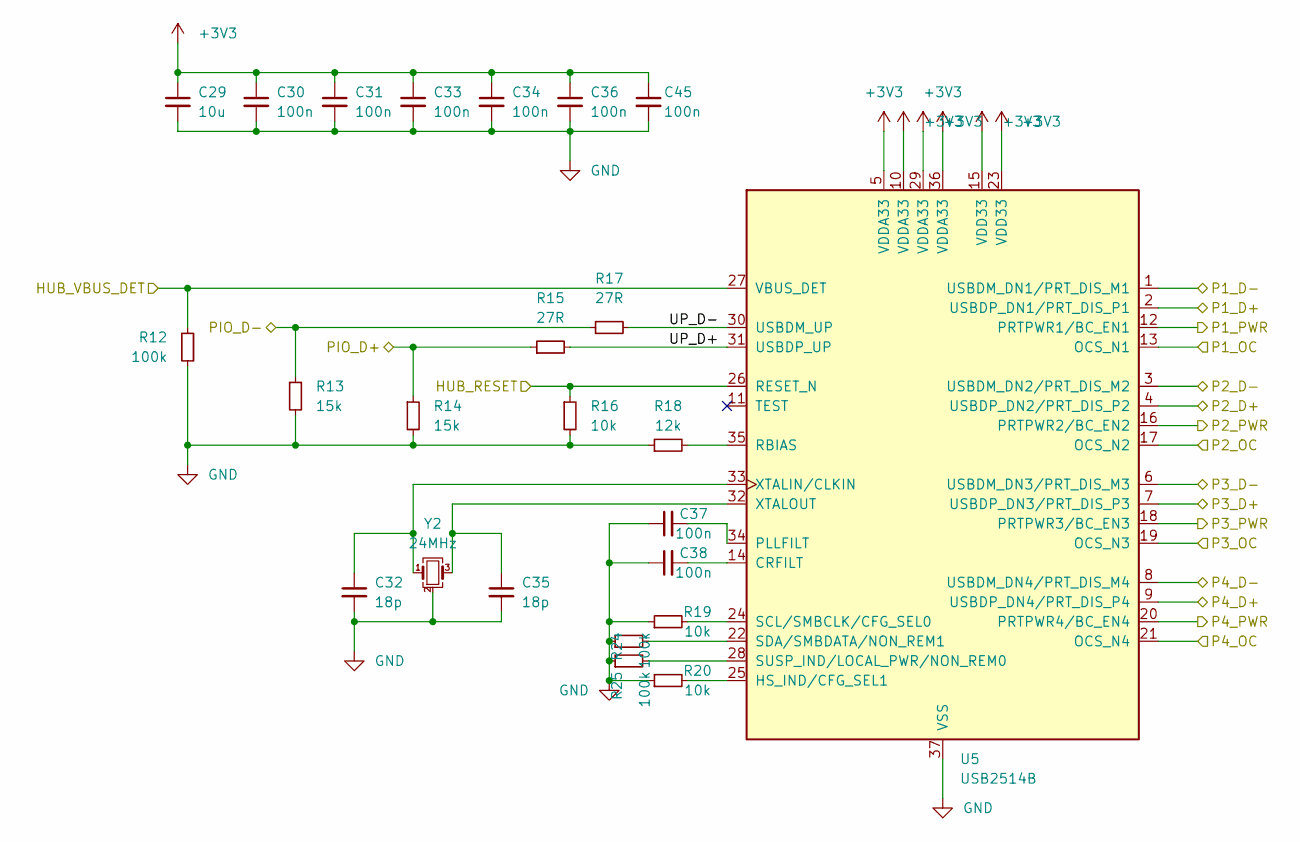
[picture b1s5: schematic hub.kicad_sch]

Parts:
C29: 10u; C_0805_2012Metric; Voltage 16V
C30, C31, C33, C34, C36, C37, C38, C45: 100n; C_0402_1005Metric; Voltage 16V
C32, C35: 18p; C_0603_1608Metric; Voltage 50V
R12, R24, R25: 100k; R_0402_1005Metric; Tolerance 5%
R13, R14: 15k; R_0402_1005Metric; Tolerance 5%
R15, R17: 27R; R_0402_1005Metric; Tolerance 1%; MPN UNI-ROYAL 0402WGF270JTCE; LCSC C25100
R16, R19, R20: 10k; R_0402_1005Metric; Tolerance 5%
R18: 12k; R_0402_1005Metric; Tolerance 1%
U5: USB2514B; QFN-36-1EP_6x6mm_P0.5mm_EP3.7x3.7mm; MPN USB2514B-AEZC-TR; LCSC C16251
Y2: 24MHz; Crystal_SMD_3225-4Pin_3.2x2.5mm; Tolerance 50ppm; MPN YXC X322524MMB4SI; LCSC C70583

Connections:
/HUB_RESET: R16.1, U5.26 (RESET_N); also elsewhere on the board
/HUB_VBUS_DET: R12.1, U5.27 (VBUS_DET); also elsewhere on the board
/P1_D+: U5.2 (USBDP_DN1/PRT_DIS_P1); also elsewhere on the board
/P1_D-: U5.1 (USBDM_DN1/PRT_DIS_M1); also elsewhere on the board
/P1_OC: U5.13 (OCS_N1); also elsewhere on the board
/P1_PWR: U5.12 (PRTPWR1/BC_EN1); also elsewhere on the board
/P2_D+: U5.4 (USBDP_DN2/PRT_DIS_P2); also elsewhere on the board
/P2_D-: U5.3 (USBDM_DN2/PRT_DIS_M2); also elsewhere on the board
/P2_OC: U5.17 (OCS_N2); also elsewhere on the board
/P2_PWR: U5.16 (PRTPWR2/BC_EN2); also elsewhere on the board
/P3_D+: U5.7 (USBDP_DN3/PRT_DIS_P3); also elsewhere on the board
/P3_D-: U5.6 (USBDM_DN3/PRT_DIS_M3); also elsewhere on the board
/P3_OC: U5.19 (OCS_N3); also elsewhere on the board
/P3_PWR: U5.18 (PRTPWR3/BC_EN3); also elsewhere on the board
/P4_D+: U5.9 (USBDP_DN4/PRT_DIS_P4); also elsewhere on the board
/P4_D-: U5.8 (USBDM_DN4/PRT_DIS_M4); also elsewhere on the board
/P4_OC: U5.21 (OCS_N4); also elsewhere on the board
/P4_PWR: U5.20 (PRTPWR4/BC_EN4); also elsewhere on the board
/PIO_D+: R14.1, R15.1; also elsewhere on the board
/PIO_D-: R13.1, R17.1; also elsewhere on the board
/hub/UP_D+: R15.2, U5.31 (USBDP_UP)
/hub/UP_D-: R17.2, U5.30 (USBDM_UP)
unnamed: C38.2, U5.14 (CRFILT)
unnamed: R20.2, U5.25 (HS_IND/CFG_SEL1)
unnamed: C37.2, U5.34 (PLLFILT)
unnamed: R18.2, U5.35 (RBIAS)
unnamed: R19.2, U5.24 (SCL/SMBCLK/CFG_SEL0)
unnamed: R24.2, U5.22 (SDA/SMBDATA/NON_REM1)
unnamed: R25.2, U5.28 (SUSP_IND/LOCAL_PWR/NON_REM0)
unnamed: C32.1, U5.33 (XTALIN/CLKIN), Y2.1
unnamed: C35.1, U5.32 (XTALOUT), Y2.3

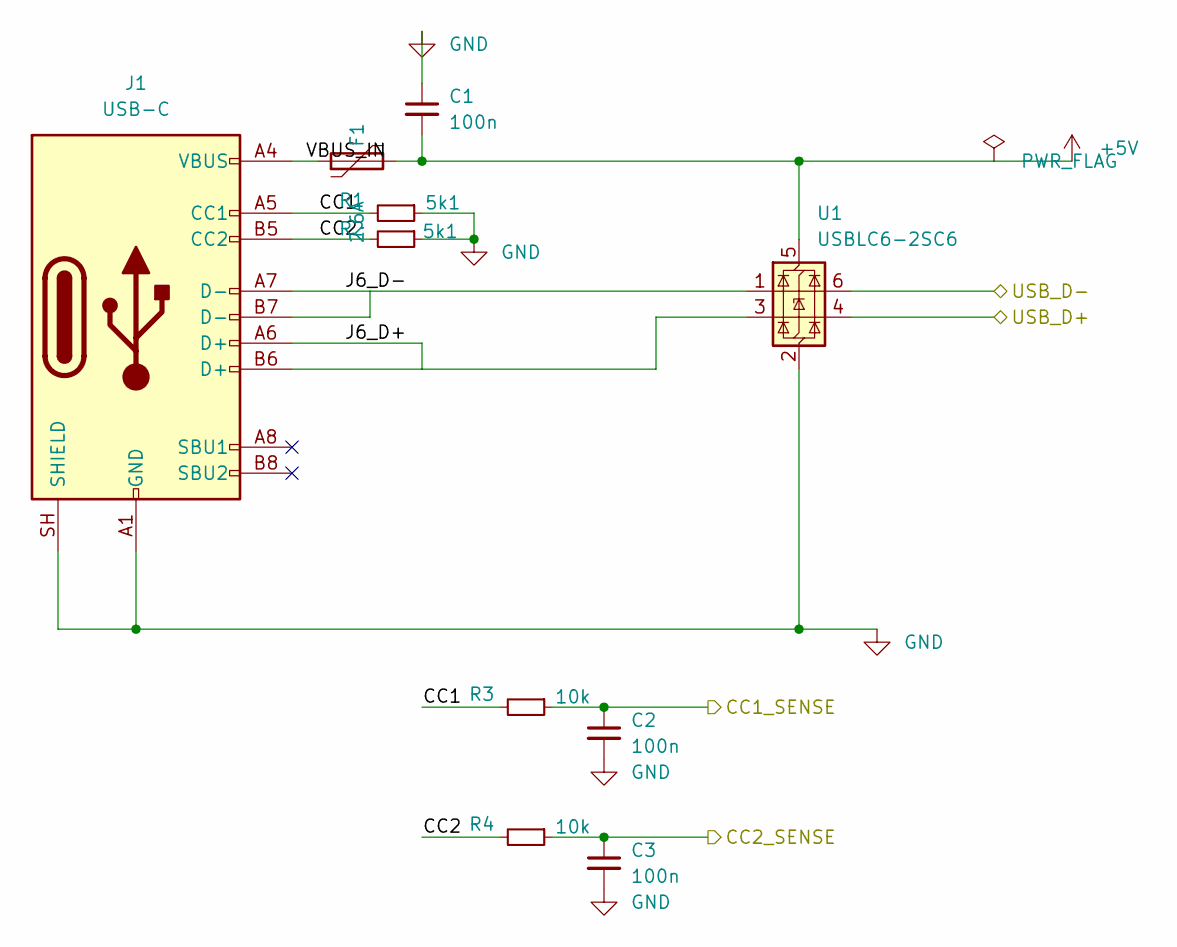
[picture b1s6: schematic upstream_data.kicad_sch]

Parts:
C1, C2, C3: 100n; C_0402_1005Metric; Voltage 50V
F1: 2.6A; Fuse_1812_4532Metric; Voltage 8V; MPN TECHFUSE mSMD260; LCSC C70127
J1: USB-C; USB_C_Receptacle_HRO_TYPE-C-31-M-12_Overhang; MPN Korean Hroparts TYPE-C-31-M-12; LCSC C165948
R1, R2: 5k1; R_0402_1005Metric; Tolerance 1%
R3, R4: 10k; R_0402_1005Metric; Tolerance 1%
U1: USBLC6-2SC6; SOT-23-6; MPN USBLC6-2SC6; LCSC C7519

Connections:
+5V: C1.2, F1.2, U1.5 (VBUS); also elsewhere on the board
/CC1_SENSE: C2.1, R3.1; also elsewhere on the board
/CC2_SENSE: C3.1, R4.1; also elsewhere on the board
/USB_D+: U1.4 (I/O2); also elsewhere on the board
/USB_D-: U1.6 (I/O1); also elsewhere on the board
/upstream_data/CC1: J1.A5 (CC1), R1.2, R3.2
/upstream_data/CC2: J1.B5 (CC2), R2.2, R4.2
/upstream_data/J6_D+: J1.A6 (D+), J1.B6 (D+), U1.3 (I/O2)
/upstream_data/J6_D-: J1.A7 (D-), J1.B7 (D-), U1.1 (I/O1)
/upstream_data/VBUS_IN: F1.1, J1.A4 (VBUS), J1.A9 (VBUS), J1.B4 (VBUS), J1.B9 (VBUS)

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
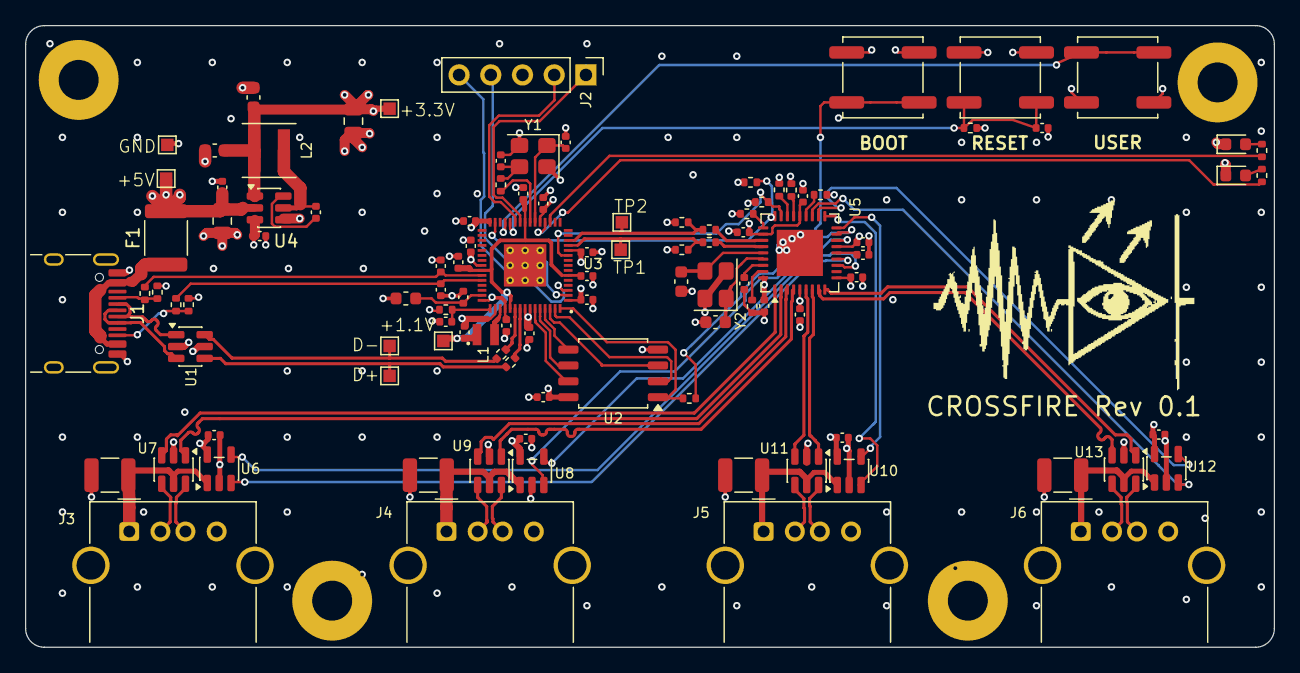
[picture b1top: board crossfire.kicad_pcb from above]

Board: 4 copper layers, 100.0 x 49.8 mm, 110 parts (0 on the bottom side), 83 nets.

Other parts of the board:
G1: crossfire_logo
